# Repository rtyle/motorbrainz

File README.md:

# motorbrainz
PCB with ESP32 microcontroller (brainz) and L298 dual full bridge (motor) driver.

The ESP32 of the [TinyPICO NANO](https://unexpectedmaker.com/shop/tinypico-nano) can be programmed by a host over the USB connection.
The ESP32 can be debugged by a host over the JTAG connection which is compatible with an [esp-prog](https://www.digikey.com/en/products/detail/espressif-systems/ESP-PROG/10259352) board, or equivalent.

The esp-prog BOOT and RST will not work because the esp-prog programming interface is not used.
The esp-prog jumper settings will have no effect.

**Warning:** The motorbrainz board ties all external ground references (12V, USB and JTAG) to the same common ground.
External 12V power should come from an isolated power supply to allow this.
The host providing USB 5V power (directly) and JTAG power (indirectly, by way of the host's USB connection to the esp-prog) should reference a common ground.

motorbrainz 5V power can either come from its 12V source (indirectly, by way of its LDO voltage regulator) or USB (directly) by setting a jumper.

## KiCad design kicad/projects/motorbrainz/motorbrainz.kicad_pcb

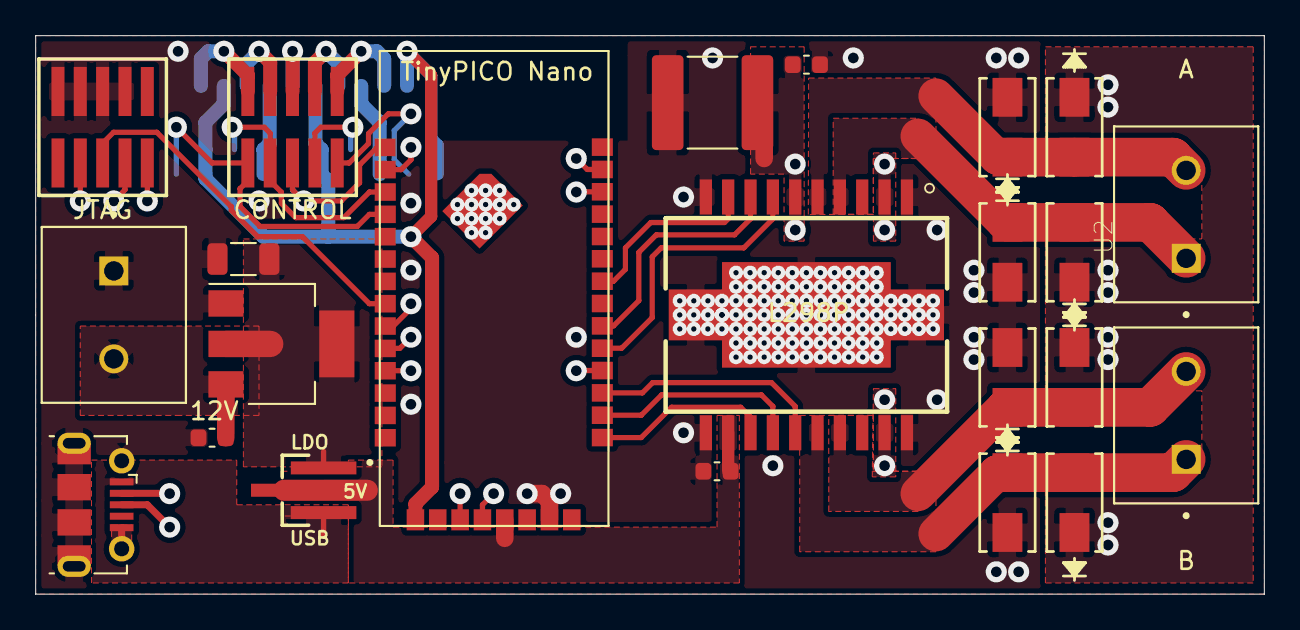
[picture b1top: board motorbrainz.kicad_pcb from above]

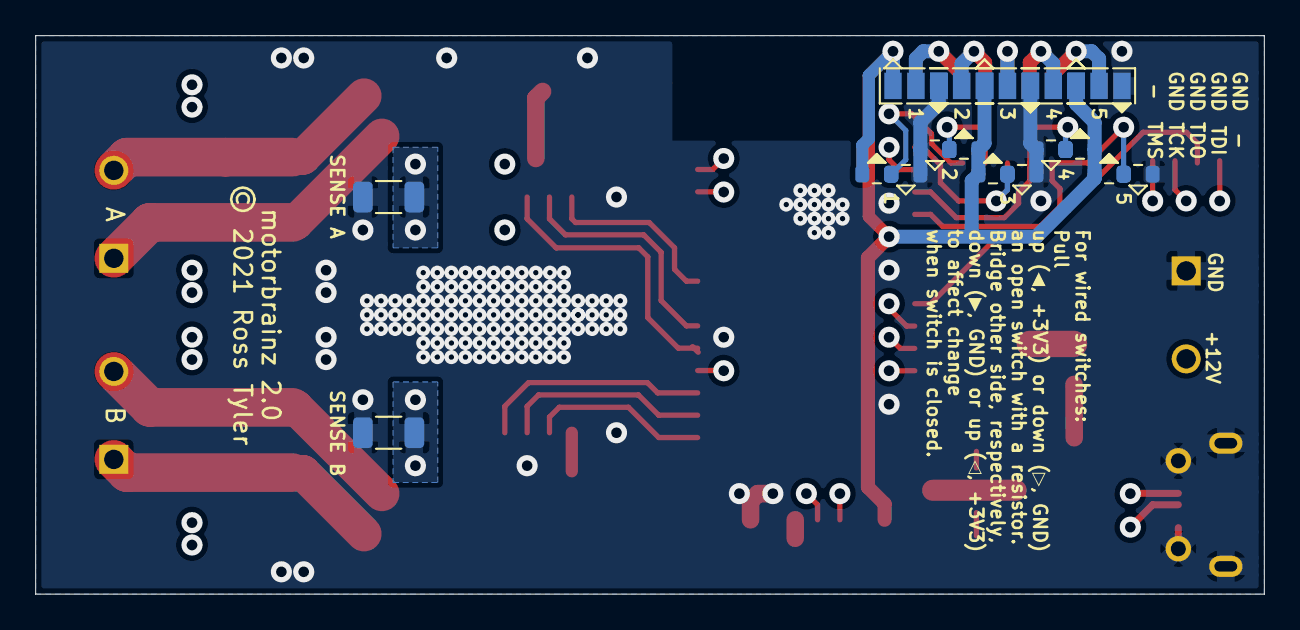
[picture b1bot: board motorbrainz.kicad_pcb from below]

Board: 4 copper layers, 69.9 x 31.8 mm, 40 parts (17 on the bottom side), 34 nets.

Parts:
C1, C3, C4: 100nF; C_0603_1608Metric
C2: 10uF; C_1206_3216Metric
C5: 47uF; C_2220_5650Metric
J1, J7: FTSH-105-01-S-DV-K; SAMTEC-FTSH-105-01-X-DV
J2: USB_B_Micro; USB_Micro-B_Molex-105017-0001
J3, J4, J5: Screw_Terminal_01x02; CONN_282836-2
J6: Conn_01x03_MountingPin; SAMTEC_FTR-103-02-S-S
JP1, JP2, JP3, JP4, JP5: SolderJumper_3_Open; SolderJumper-3_P1.3mm_Open_Pad1.0x1.5mm
R1, R2: 0.1; R_1206_3216Metric
R3, R4, R5, R6, R7, R8, R9, R10, R11, R12: 10k; R_0603_1608Metric
U1: tinyPICO_Nano; TinyPICO_Nano
U2: L298P; SOIC127P1420X360-20N
U3, U4, U5, U6, U7, U8, U9, U10: CDBA240LL-HF
U11: LD1117S50TR_SOT223; SOT-223-3_TabPin2

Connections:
+3V3: JP1.3, JP2.3, JP3.3, JP4.3, JP5.3, R3.1, R5.1, R7.1, R9.1, R11.1, U1.8
+5V: C3.1, J6.2, U1.4, U2.12
+12V: C1.1, C4.1, C5.1, J3.2, U2.6, U3.1, U5.1, U7.1, U9.1, U11.3
/+5VFAR: J2.1, J6.3
/+5VNEAR: C2.1, J6.1, U11.2
/D+: J2.3, U1.6
/D-: J2.2, U1.5
/ENA: U1.28, U2.8
/ENB: U1.24, U2.14
/INA1: U1.27, U2.7
/INA2: U1.30, U2.9
/INB1: U1.23, U2.13
/INB2: U1.25, U2.15
/OUTA1: J4.1, U2.4, U3.2, U4.1
/OUTA2: J4.2, U2.5, U5.2, U6.1
/OUTB1: J5.1, U2.16, U7.2, U8.1
/OUTB2: J5.2, U2.17, U9.2, U10.1
/SENA: R1.1, U1.35, U2.2
/SENB: R2.1, U1.21, U2.19
/SW1B: J7.1, JP1.2
/SW1R: J7.2, R3.2, R4.1, U1.26
/SW2B: J7.3, JP2.2
/SW2R: J7.4, R5.2, R6.1, U1.34
/SW3B: J7.5, JP3.2
/SW3R: J7.6, R7.2, R8.1, U1.22
/SW4B: J7.7, JP4.2
/SW4R: J7.8, R9.2, R10.1, U1.20
/SW5B: J7.9, JP5.2
/SW5R: J7.10, R11.2, R12.1, U1.19
/TCK: J1.4, U1.13
/TDI: J1.8, U1.12
/TDO: J1.6, U1.15
/TMS: J1.2, U1.14
GND: C1.2, C2.2, C3.2, C4.2, C5.2, J1.3, J1.5, J1.7, J1.9, J2.5, J2.6, J3.1, JP1.1, JP2.1, JP3.1, JP4.1, JP5.1, R1.2, R2.2, R4.2, R6.2, R8.2, R10.2, R12.2, U1.2, U2.1, U2.10, U2.11, U2.20, U2.21, U2.22, U2.23, U4.2, U6.2, U8.2, U10.2, U11.1

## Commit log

2021-03-18 gerber
2021-04-29 2.0: replace ESP-PROG with USB connecter to use TinyPICO NANO USB to serial converter
2021-04-29 export schematic as PDF
2021-04-30 Update README.md
    USB programming interface
2021-05-01 thicken USB power traces

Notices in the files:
kicad/projects/motorbrainz/motorbrainz.kicad_pcb:
© 2021 Ross Tyler
parts and their libraries:
Copyright 2016 Accelerated Designs. All rights reserved.
